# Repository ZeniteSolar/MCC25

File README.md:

# MCC25
MCC25  
MPPT Battery charger  

| Input Voltage     | 0 ~ 21 V  |
| ----------------: | :-------- |
|   Output Voltage  | 21 ~ 40V  |
| Output Power      | 200 W     |
| Efficiency        | > 90%     |

## Modelo 3D

## Placa Soldada

# Guia de montagem da placa MCC25

A placa foi projetada para facilitar a montagem, mas é necessário tomar alguns cuidados devido a algumas alterações no projeto.

## Passo a Passo

| Passo | Instruções | Imagem |
|------|------------|--------|
| **1** | Realizar a troca do resistor R20 de 15Ω para um resistor de 4.7Ω. |  |
| **2** | Isolar o pino de referência do sensor de efeito HALL "U2" raspando as trilhas conectadas ao GND, em ambos os lados da placa.( Somente raspar as trilhas relacionadas ao pino de referência, o resto manter igual ) |  |
| **3** | Não realizar a solda do resistor R7, pois ele será soldado em outro local da placa. |  |
| **4** | Após isolar o pino de referência do sensor de efeito HALL, realizar a solda dele normalmente. Em seguida, soldar um resistor de 150Ω entre o pino de referência e o output do sensor. (Certificar-se de que não há curto-circuito). |  |
| **5** | Montagem do snubber: verificar a necessidade, mas a dica de montagem é usar um diodo TVS Schottky 100V, capacitor de 4.7nF 100V e resistor 4.7KΩ 3W. |  |

## Testes

Em processo...

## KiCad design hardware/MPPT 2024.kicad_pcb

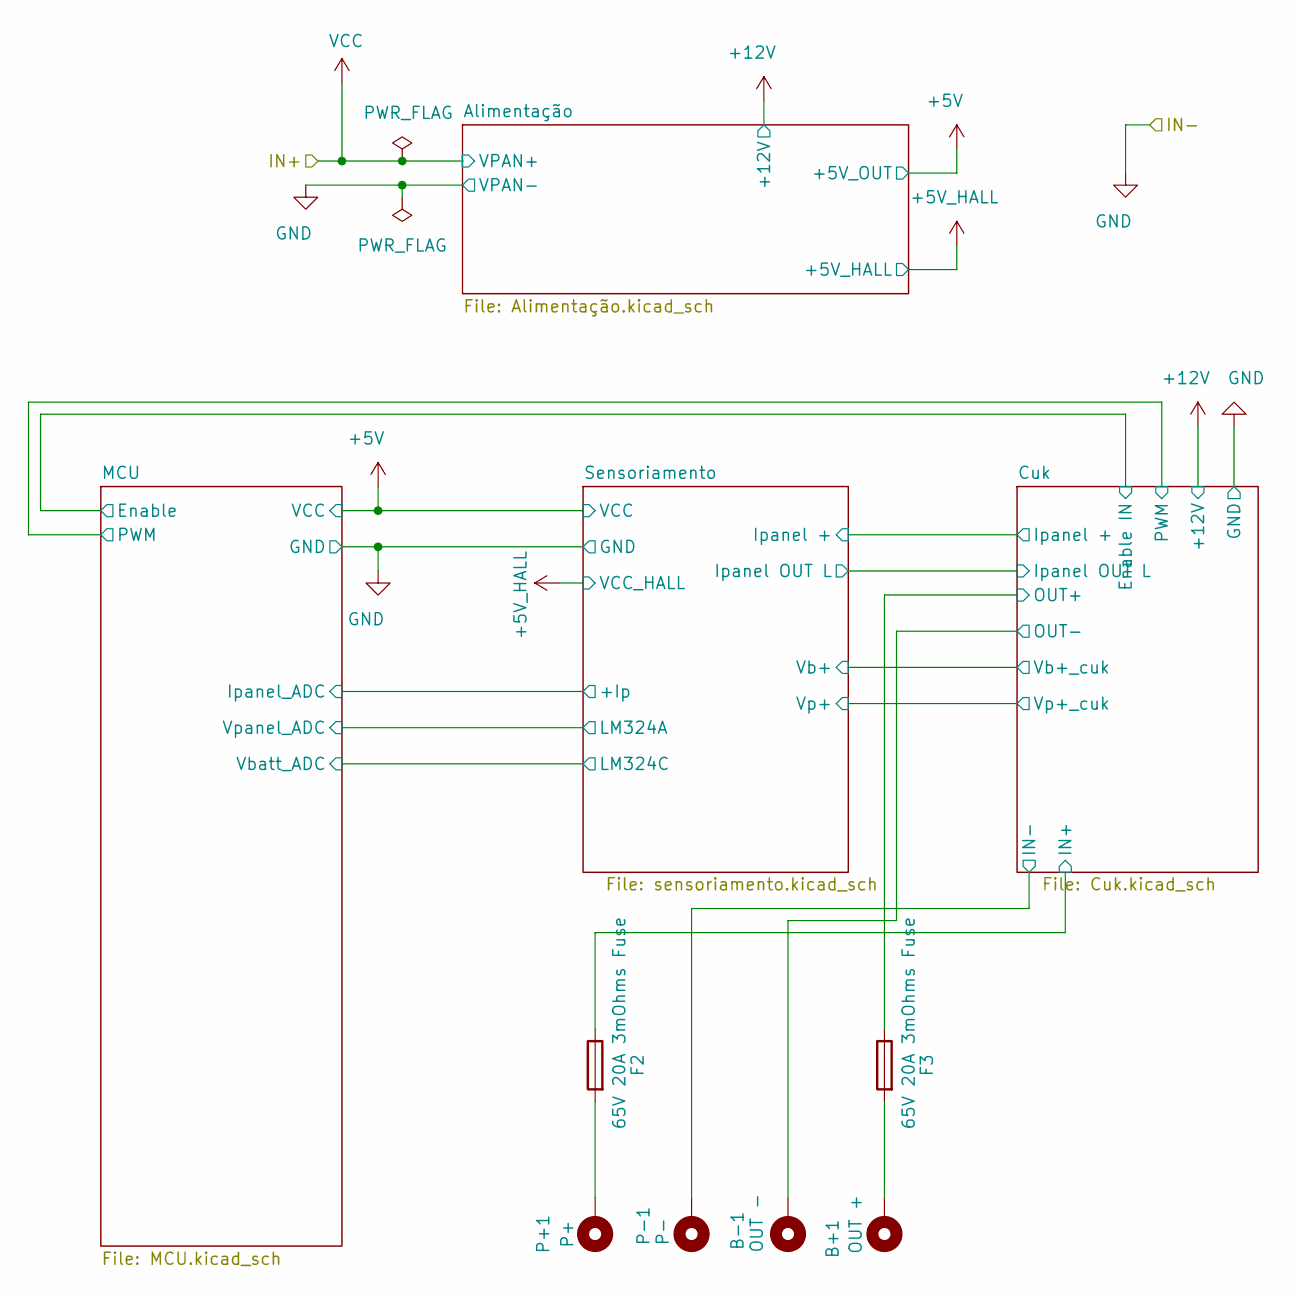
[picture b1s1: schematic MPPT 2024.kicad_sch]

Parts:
B+1: OUT +; FURO_PAN_BAT
B-1: OUT -; FURO_PAN_BAT
F2, F3: 65V 20A 3mOhms Fuse; FUSE_6125
P+1: P+; FURO_PAN_BAT
P-1: P-; FURO_PAN_BAT

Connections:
/Cuk/OUT-: B-1.1; also elsewhere on the board
GND: F3.1, P-1.1; also elsewhere on the board
unnamed: B+1.1, F3.2
unnamed: F2.2, P+1.1
VCC: F2.1; also elsewhere on the board

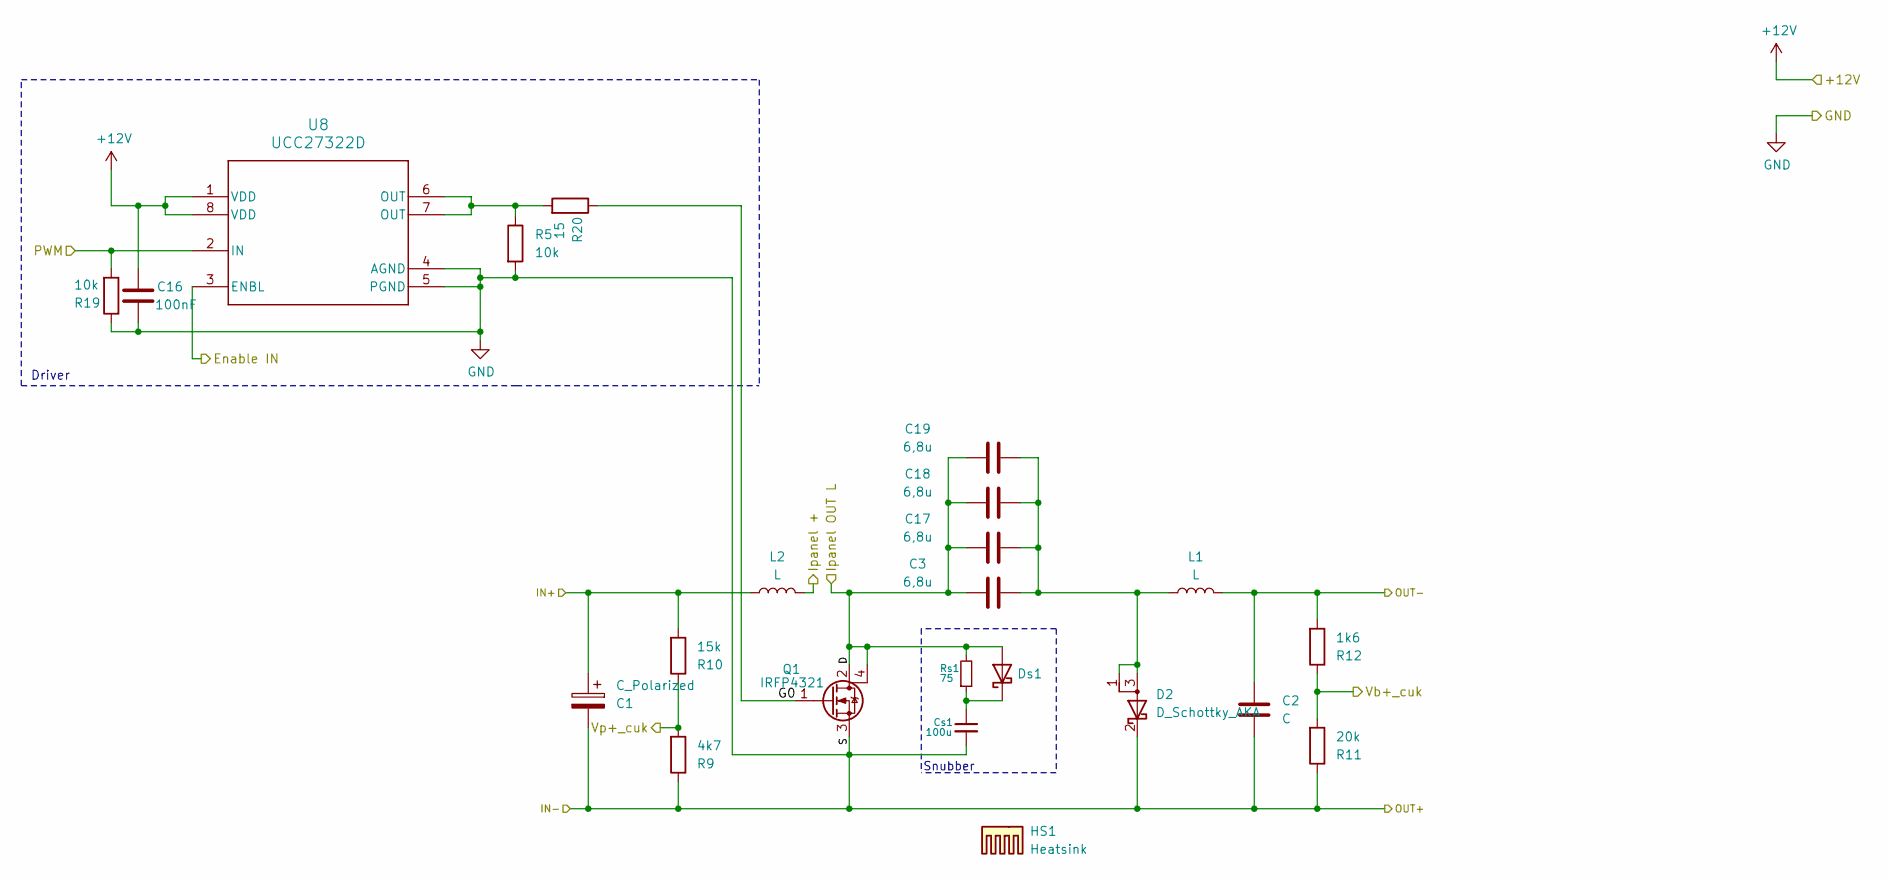
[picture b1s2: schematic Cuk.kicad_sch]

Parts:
C1: C_Polarized
C2: C
C3, C17, C18, C19: 6,8u; CP_Elec_8x11.9
C16: 100nF; C_0805_2012Metric_Pad1.18x1.45mm_HandSolder
Cs1: 100u; C_0805_2012Metric_Pad1.18x1.45mm_HandSolder; Voltage 200V; Tolerance 10%
D2: D_Schottky_AKA; TO-220-3_Horizontal_TabUp
Ds1: D_Schottky; D_SMA
HS1: Heatsink; DISSIPADOR
L1, L2: L; INDUTOR E30_14
Q1: IRFP4321; TO-247-3_Horizontal_TabUp
R5, R19: 10k; R_0805_2012Metric_Pad1.20x1.40mm_HandSolder
R9: 4k7; R_0805_2012Metric_Pad1.20x1.40mm_HandSolder
R10: 15k; R_0805_2012Metric_Pad1.20x1.40mm_HandSolder
R11: 20k; R_0805_2012Metric_Pad1.20x1.40mm_HandSolder
R12: 1k6; R_0805_2012Metric_Pad1.20x1.40mm_HandSolder
R20: 15; R_0805_2012Metric_Pad1.20x1.40mm_HandSolder
Rs1: 75; R_2512_6332Metric_Pad1.40x3.35mm_HandSolder; Tolerance 10%
U8: UCC27322D; SOIC-8_3.9x4.9mm_P1.27mm

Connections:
+12V: C16.2, U8.1 (VDD), U8.8 (VDD); also elsewhere on the board
/Cuk/D: C3.1, C17.1, C18.1, C19.1, Ds1.2 (A), Q1.2 (D), Q1.4 (D), Rs1.2; also elsewhere on the board
/Cuk/Enable IN: U8.3 (ENBL); also elsewhere on the board
/Cuk/G0: Q1.1 (G), R20.1
/Cuk/Ipanel +: L2.2; also elsewhere on the board
/Cuk/OUT-: C2.1, L1.2, R12.2; also elsewhere on the board
/Cuk/PWM: R19.2, U8.2 (IN); also elsewhere on the board
/Cuk/Vb+_cuk: R11.2, R12.1; also elsewhere on the board
/Cuk/Vp+_cuk: R9.2, R10.1; also elsewhere on the board
GND: C1.2, C2.2, C16.1, Cs1.2, D2.2 (K), Q1.3 (S), R5.2, R9.1, R11.1, R19.1, U8.4 (AGND), U8.5 (PGND); also elsewhere on the board
unnamed: C3.2, C17.2, C18.2, C19.2, D2.1 (A), D2.3 (A), L1.1
unnamed: Cs1.1, Ds1.1 (K), Rs1.1
unnamed: R5.1, R20.2, U8.6 (OUT), U8.7 (OUT)
VCC: C1.1, L2.1, R10.2; also elsewhere on the board

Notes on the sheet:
Snubber
Driver

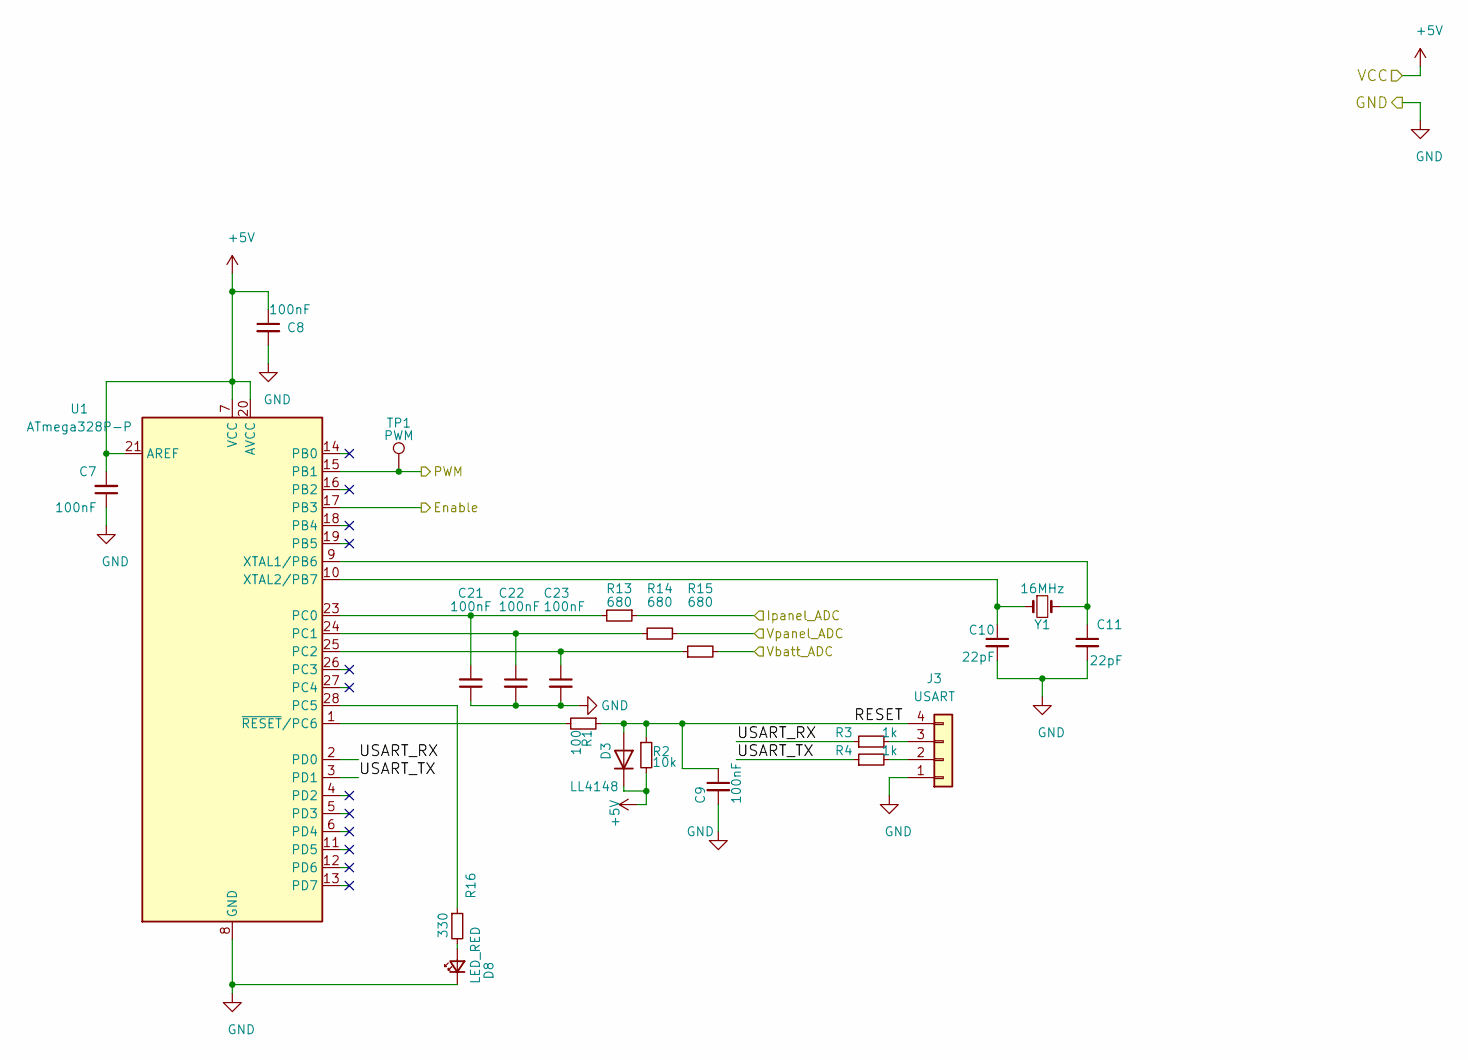
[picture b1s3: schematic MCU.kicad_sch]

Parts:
C7, C8, C9, C21, C22, C23: 100nF; C_0805_2012Metric_Pad1.18x1.45mm_HandSolder
C10, C11: 22pF; C_0805_2012Metric_Pad1.18x1.45mm_HandSolder
D3: LL4148; D_MiniMELF_Handsoldering
D8: LED_RED; LED_0805_2012Metric_Pad1.15x1.40mm_HandSolder
J3: USART; PinSocket_1x04_P2.54mm_Horizontal
R1: 100; R_0805_2012Metric_Pad1.20x1.40mm_HandSolder
R2: 10k; R_0805_2012Metric_Pad1.20x1.40mm_HandSolder
R3, R4: 1k; R_0805_2012Metric_Pad1.20x1.40mm_HandSolder
R13, R14, R15: 680; R_0805_2012Metric_Pad1.20x1.40mm_HandSolder
R16: 330; R_0805_2012Metric_Pad1.20x1.40mm_HandSolder
TP1: PWM; TestPoint_Pad_2.0x2.0mm
U1: ATmega328P-P; DIP-28_W7.62mm
Y1: 16MHz; Crystal_HC49-U_Vertical

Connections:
+5V: C7.2, C8.1, D3.1 (K), R2.2, U1.7 (VCC), U1.20 (AVCC), U1.21 (AREF); also elsewhere on the board
/Cuk/Enable IN: U1.17 (PB3); also elsewhere on the board
/Cuk/PWM: TP1.1, U1.15 (PB1); also elsewhere on the board
/MCU/Ipanel_ADC: R13.1; also elsewhere on the board
/MCU/RESET: C9.1, D3.2 (A), J3.4, R1.1, R2.1
/MCU/USART_RX: R3.1, U1.2 (PD0)
/MCU/USART_TX: R4.1, U1.3 (PD1)
/MCU/Vbatt_ADC: R15.2; also elsewhere on the board
/MCU/Vpanel_ADC: R14.2; also elsewhere on the board
GND: C7.1, C8.2, C9.2, C10.2, C11.2, C21.1, C22.2, C23.2, D8.1 (K), J3.1, U1.8 (GND), U1.22 (GND); also elsewhere on the board
unnamed: D8.2 (A), R16.2
unnamed: J3.2, R4.2
unnamed: J3.3, R3.2
unnamed: C21.2, R13.2, U1.23 (PC0)
unnamed: C22.1, R14.1, U1.24 (PC1)
unnamed: C23.1, R15.1, U1.25 (PC2)
unnamed: R16.1, U1.28 (PC5)
unnamed: C11.1, U1.9 (XTAL1/PB6), Y1.2
unnamed: C10.1, U1.10 (XTAL2/PB7), Y1.1
unnamed: R1.2, U1.1 (~RESET/PC6)

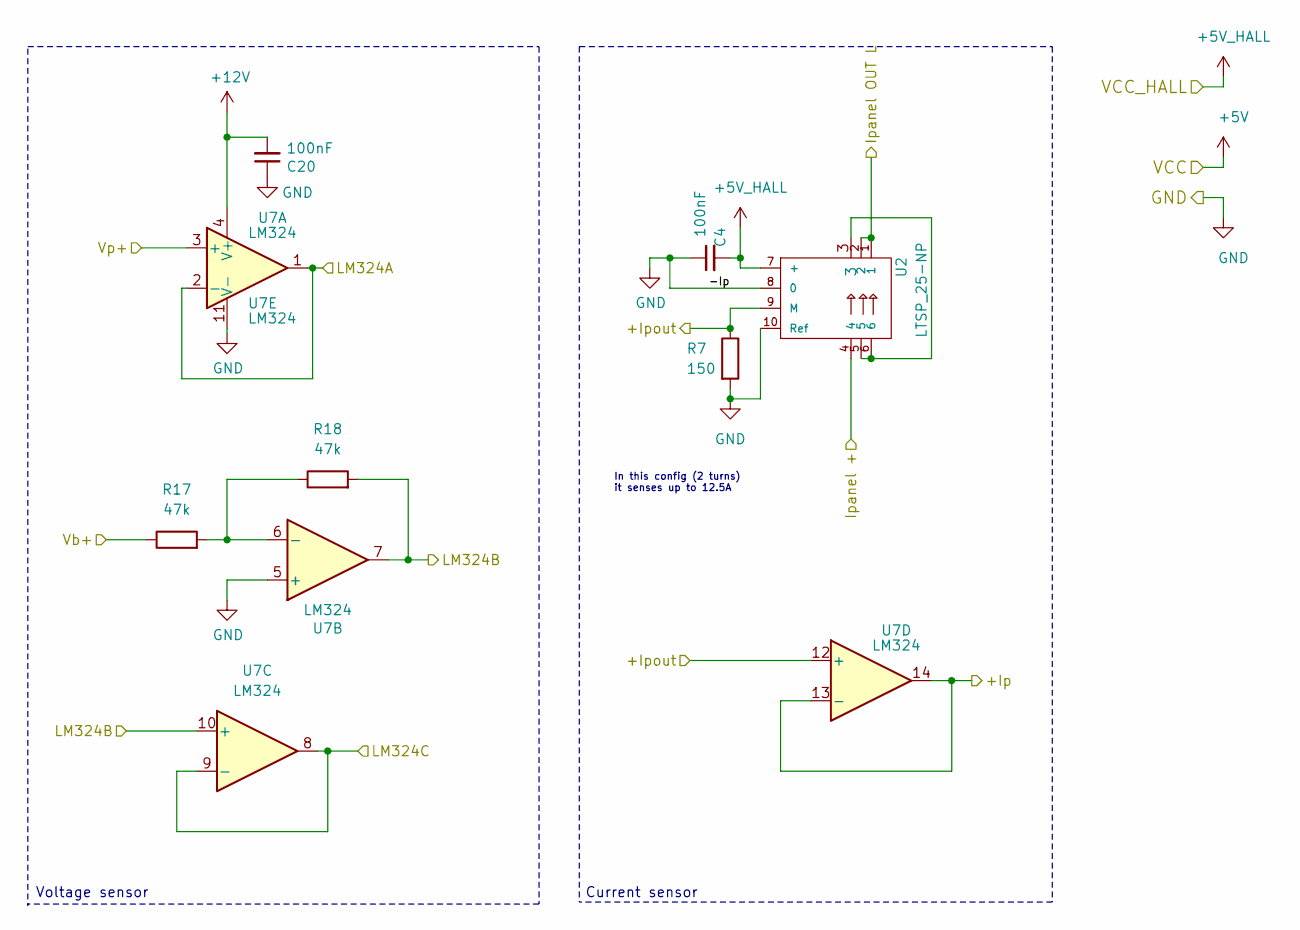
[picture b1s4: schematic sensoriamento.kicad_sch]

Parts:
C4, C20: 100nF; C_0805_2012Metric_Pad1.18x1.45mm_HandSolder
R7: 150; R_0805_2012Metric_Pad1.20x1.40mm_HandSolder
R17, R18: 47k; R_0805_2012Metric_Pad1.20x1.40mm_HandSolder
U2: LTSP_25-NP
U7: LM324; DIP-14_W7.62mm_LongPads

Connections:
+5V_HALL: C4.2, U2.7 (+); also elsewhere on the board
+12V: C20.2, U7.4 (V+); also elsewhere on the board
/Cuk/D: U2.1, U2.2; also elsewhere on the board
/Cuk/Ipanel +: U2.4; also elsewhere on the board
/Cuk/Vb+_cuk: R17.1; also elsewhere on the board
/Cuk/Vp+_cuk: U7.3 (+); also elsewhere on the board
/MCU/Ipanel_ADC: U7.13 (-), U7.14; also elsewhere on the board
/MCU/Vbatt_ADC: U7.8, U7.9 (-); also elsewhere on the board
/MCU/Vpanel_ADC: U7.1, U7.2 (-); also elsewhere on the board
/Sensoriamento/+Ipout: R7.1, U2.9 (M), U7.12 (+)
/Sensoriamento/LM324B: R18.2, U7.7, U7.10 (+)
GND: C4.1, C20.1, R7.2, U2.8 (0), U2.10 (Ref), U7.5 (+), U7.11 (V-); also elsewhere on the board
unnamed: U2.3, U2.5, U2.6
unnamed: R17.2, R18.1, U7.6 (-)

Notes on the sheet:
In this config (2 turns) it senses up to 12.5A
Voltage sensor
Current sensor

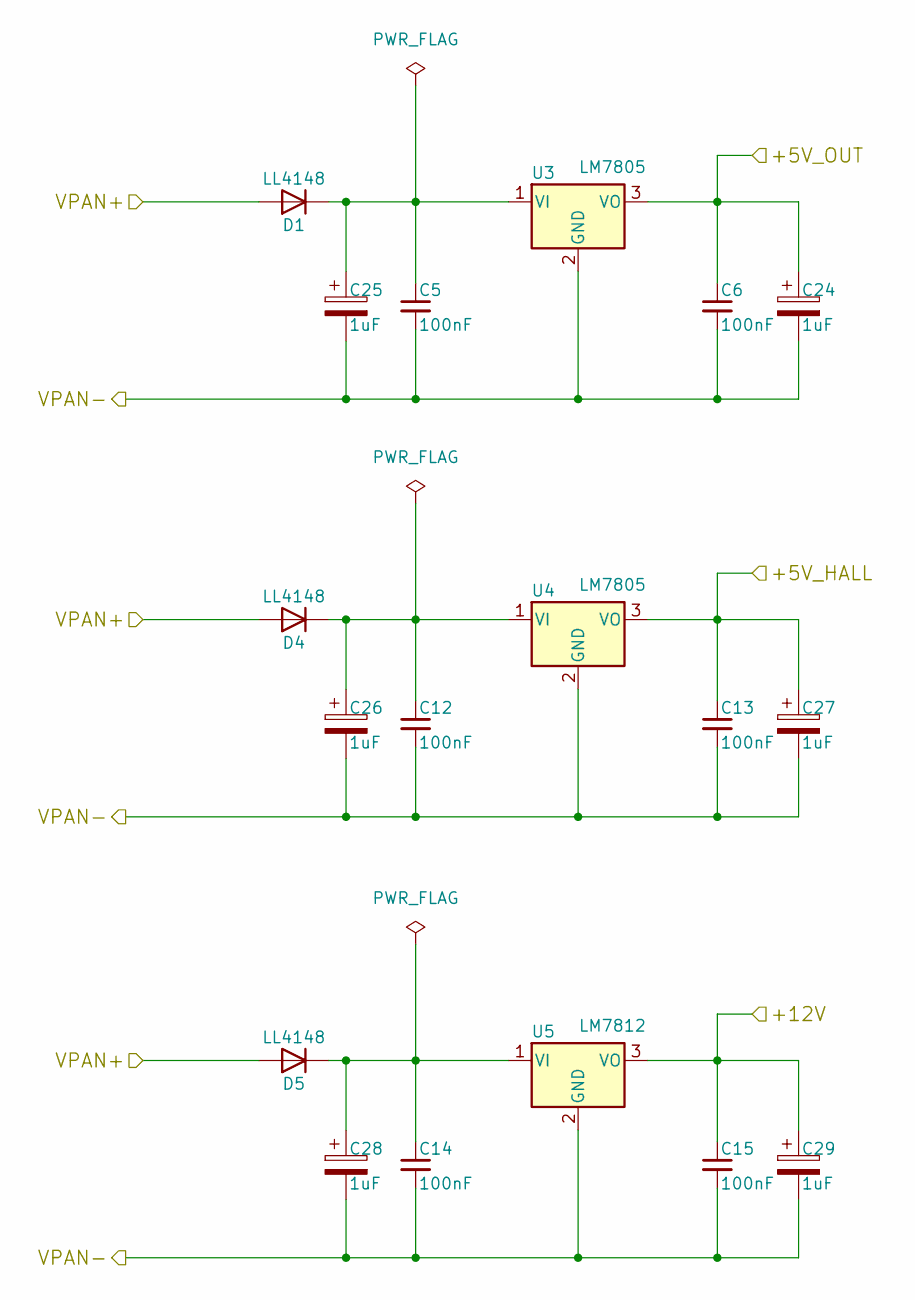
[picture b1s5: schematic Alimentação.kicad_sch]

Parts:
C5, C6, C12, C13, C14, C15: 100nF; C_0805_2012Metric_Pad1.18x1.45mm_HandSolder
C24, C25, C26, C27, C28, C29: 1uF; CP_EIA-6032-15_Kemet-U_Pad2.25x2.35mm_HandSolder
D1, D4, D5: LL4148; D_MiniMELF_Handsoldering
U3, U4: LM7805; TO-220-3_Horizontal_TabDown
U5: LM7812; TO-220-3_Horizontal_TabDown

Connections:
+5V: C6.1, C24.1, U3.3 (VO); also elsewhere on the board
+5V_HALL: C13.1, C27.1, U4.3 (VO); also elsewhere on the board
+12V: C15.1, C29.1, U5.3 (VO); also elsewhere on the board
GND: C5.2, C6.2, C12.2, C13.2, C14.2, C15.2, C24.2, C25.2, C26.2, C27.2, C28.2, C29.2, U3.2 (GND), U4.2 (GND), U5.2 (GND); also elsewhere on the board
unnamed: C5.1, C25.1, D1.1 (K), U3.1 (VI)
unnamed: C12.1, C26.1, D4.1 (K), U4.1 (VI)
unnamed: C14.1, C28.1, D5.1 (K), U5.1 (VI)
VCC: D1.2 (A), D4.2 (A), D5.2 (A); also elsewhere on the board

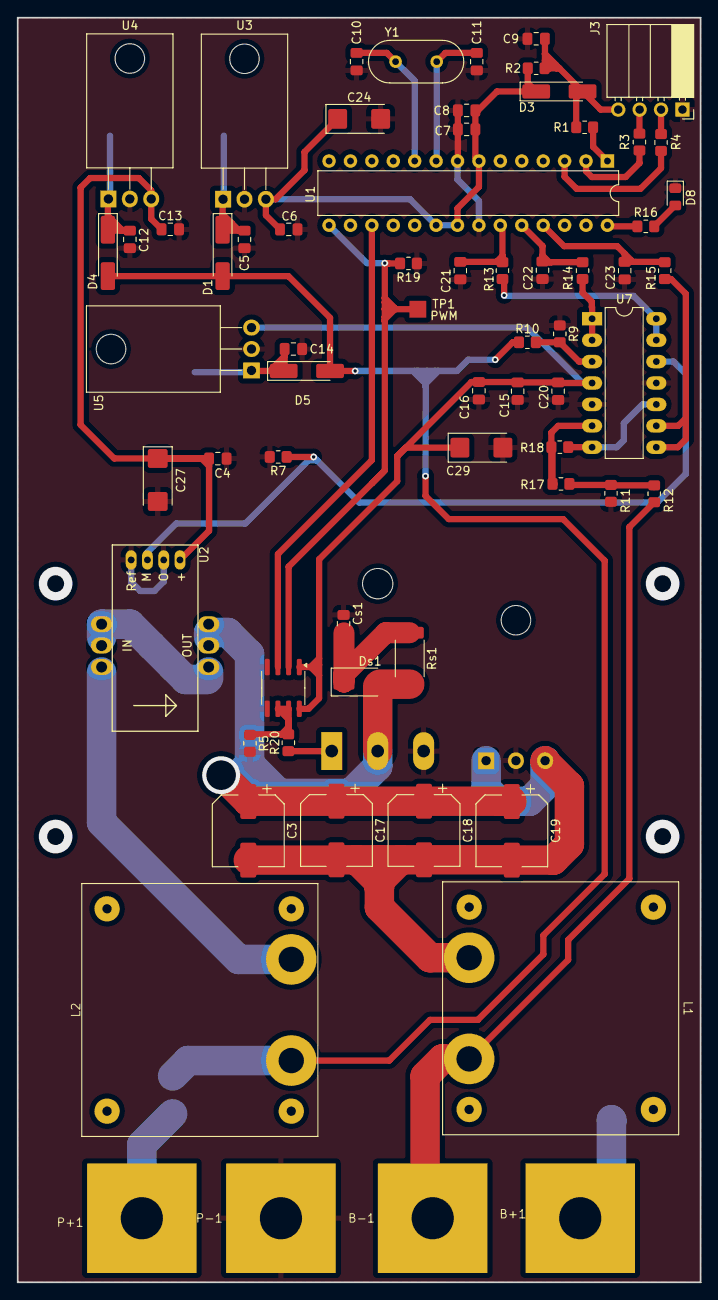
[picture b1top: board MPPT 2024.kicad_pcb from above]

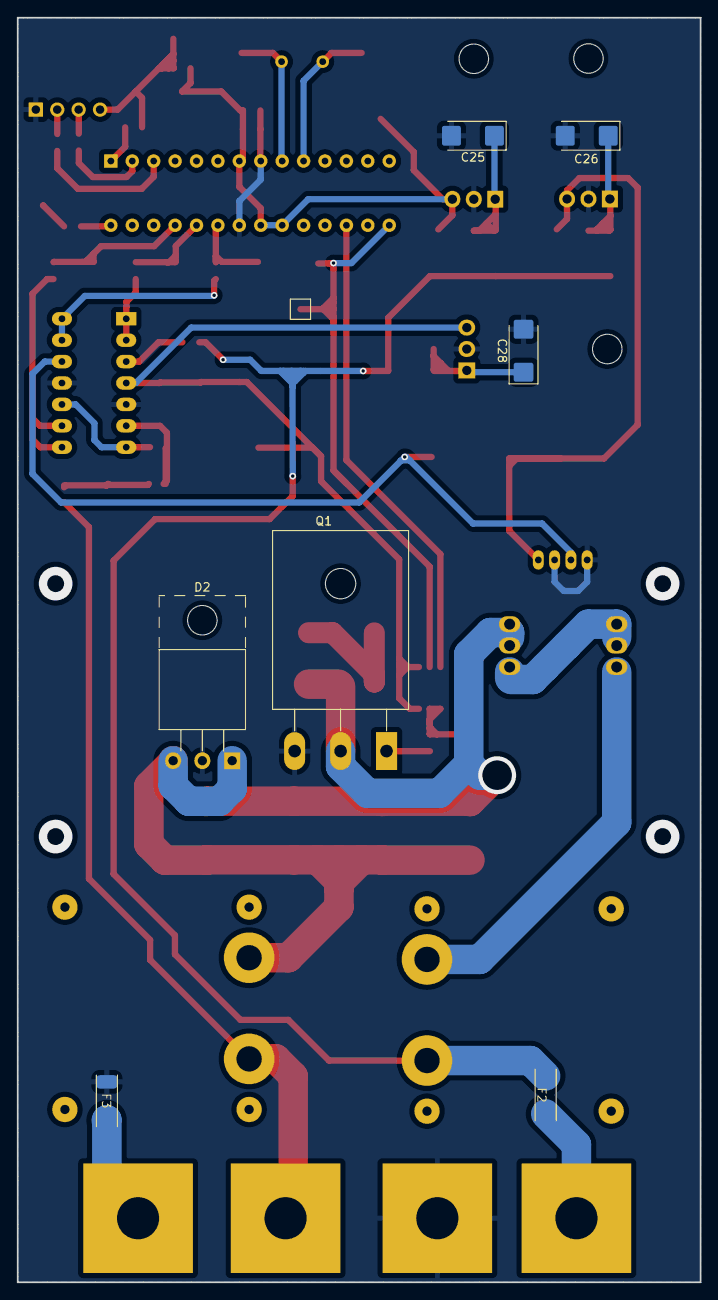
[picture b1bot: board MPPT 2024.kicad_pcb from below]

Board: 2 copper layers, 81.0 x 150.0 mm, 73 parts (8 on the bottom side), 41 nets.

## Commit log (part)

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2025-02-13 Removing Zone Identifier trash
2025-03-08 Atualizações no firmware: adicionado sweep durante o PeO
2025-03-14 Create Images
2025-03-14 Update Images
2025-03-14 Adicionando images à main
2025-03-14 Rename Real_Side.jpeg to images/Real_Side.jpeg
2025-03-14 Rename Real_bottom.jpeg to images/Real_bottom.jpeg
2025-03-14 Rename Real_top.jpeg to images/Real_top.jpeg
2025-03-14 Rename bottom.png to images/bottom.png
2025-03-14 Rename top.png to images/top.png
2025-03-14 Rename Images to images/Images
2025-03-14 Rename imagem_2025-03-14_160552225.png to R20.png
2025-03-14 ADD R20.png
2025-03-14 Add Hall_reference.jpeg
2025-03-14 ADD R7
2025-03-14 Add RES_HALL.jpeg
2025-03-14 Add Snubber.jpeg
2025-03-17 Upload images
2025-03-17 Create simulation
2025-04-02 add denit
2025-05-09 add gitignore
2025-05-09 melhorias para o algoritmo de controle
2025-05-12 wdt configurado
2025-05-12 wdt trigger if duty is stuck
2025-05-15 linearization output voltage
2025-05-17 battery disconnection
2025-06-08 change in control time
2025-06-14 fine-tune perturb and observe
